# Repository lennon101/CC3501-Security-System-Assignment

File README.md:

# CC3501-Security-System-Assignment

##ABSTRACT
The purpose of this project was to investigate, design and implement an indoor security system that involved wireless communication, motion detection, image processing as well as additional features including a website with a video stream and control features. The projects objective has been to innovate an easy to use and affordable system ready for consumer use. This technical report provides and overview of the investigation, design and implementation done to deploy the project prototype.

##CC3501
- GROUP 5: Dane Lennon, Michael Grasso, Stuart Hinchliff, Stephanie Baker

##Project Features and Functionality
This system involves the integration of both hardware and software. It features a custom microprocessor PCB with a PIR motion detecting sensor communicating with a Raspberry Pi via XBee communications.
The features of this project include:
- Webserver application interface with full functionality
- The ability to arm and disarm the system
- Low power initial motion detection using a PIR sensor
- A second check for motion detection with complex image detection algorithms
- Voice configuration mode 
- Ability to email and save screenshots

##Hardware Design
###Printed Circuit Board Design
When designing this system, it was a priority that it must be as small and efficient as possible and only include the minimum number of necessary hardware features on the PCB, these included:
- PIR sensor for motion detection,
- LED to indicate motion detection 
- USB 2.0 port for power and necessary power supply regulations 
- Xbee for Zigbee communication
- JTAG header for SEGA programming 
- Battery holder for backup power

To reduce the size of this board further, a custom microprocessor board was designed to replace the standard shield for a Freescale Board. The Freescale FRDM-K20D50M schematic was used as a reference through the design process. Therefore, the microprocessor design, including the clock source and decoupling capacitor designs, was executed similarly to a professional board design. Figure 3 shows the completed PCB. 

###Central Hub and Peripherals
Implementing a security system with advanced features such as image processing and voice control was a task that could only be performed using a highly functional and heavily customizable device. The obvious choice was a Raspberry Pi, with capabilities of a small computer running the Linux operating system. The Raspberry Pi offers all of the features required by the group to design the central hub. Additionally, many open-source libraries are available for Linux to assist with the necessary features of the system such as the development of image processing, voice control and video streaming.

The Raspberry Pi B+ model features two USB ports and a 3.5mm audio jack, allowing the group to attach all required devices with ease. Additionally, a ribbon camera designed specifically for the Raspberry Pi is available, allowed for easy connection of a camera. The list of peripherals used in this project are:
Raspberry Pi Camera Board 
- USB 2.0 Microphone 
- Wi-Pi USB 2.0 Connector
- Powered USB 2.0 Hub

##Software Design
Robust was fundamental to the project. The system integrates scripts in C, C++, Python, HTML, JavaScript, and many external frameworks and libraries. The two main scripts were the C++ code running the main hub, and the Python code operating the webserver. Details of the functionality are described below.

###Server and Web-application
In order to appropriately develop the project, the target audience and their needs were carefully considered. It was assumed that average users would have no prior technical experience with embedded systems, so the software was designed to be user friendly.
A number of control methods were contemplated in the design process, including the use of a Bluetooth or web application. Upon review of similar products available it was determined that a web application provided the flexibility desired with: 
- Range of use (only an internet connection required 
- Security (authentication methods)
- Interface (intuitive GUI)
- Accessibility on a range of devices
- Potential for expansion
 
Various frameworks were considered to host the server. Due to its popularity and power, the lightweight, Python-based, framework called Flask was chosen. Further, a Bootstrap template was used for the webpage structure to improve the visual appeal and enhance user experience.

####Video Streaming
Surveillance is becoming increasingly prevalent in security systems and was the main drive for developing a web application. The implementation of this was inspired by Miguel Grinberg’s live video stream [1], which demonstrated how versatile Flask could be.
The main complication with using Python was its compatibility with the existing C++ code. It was found that a conflict occurred when attempting to access the camera from Python (for video streaming) and C++ (for image processing) scripts simultaneously. To overcome this, it was decided that saving an image from the C++ code and loading it to Python was the most feasible option. This came with a variety of advantages and disadvantages. It reduced the complexity of the code and it also provided a saved image for use in other processes, but the continuous read/write of images does consume system time. Sockets were also considered, but for image matrices proved complicated and prone to problem.

####Web-Application Control
The website comprises of three main pages: dashboard, view screenshots, and email configuration. The functionality of the website is as follows: (see Figure 2 for flowchart):
- Dashboard: View the live stream and execute available commands.
- Arm (Default): Receive data from the PCB. If a 1 (motion detected) is received image processing code is executed and an email is sent to the saved address.
- Disarm: Stop receiving data from the PCB.
- Save a SnapShot: Capture image of the live stream.
- Email a SnapShot: Send an email of the current image to the saved address.
- Enable Voice: Turn on voice control, allowing the user to configure via voice. o Disable Voice (Default): Turn off voice control.

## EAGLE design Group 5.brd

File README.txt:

To run the code, do it the way we do in labs: 
> $ cd SecuritySystem/build
> $ ./main

The main.cpp file - photo capture:
> There is one function that takes one photo as input and simply saves it
> This is the photo we will use for our stream
> It doesn't matter how often you upload the photo because there will always be an
  image with the right name there
> But the main loop is capturing an image every 10 loops
> The image is called "streamImage.jpg" and is found in the src directory

The main.cpp file - motion detection:
> There is one function that takes three frames and compares them for motion
> The difference between frame 1 and 3 is taken (3 being most recent capture)
> The difference between frame 2 and 3 is taken
> An "and" operation is performed on the differences so that only pixels that
  were changed in difference 1 AND difference 2 are counted (this eliminates
  a LOT of background noise)
> Then the image is converted to greyscale and thresholded 
> Thresholding could be upped from 25 to 30, but I found best accuracy with 25
  in my bedroom
> A very small amount of background noise may occur when a fan is on (I found that
  the clothes on my clothes line were moving just enough to trigger about 2-8 pixels
  of "difference") so the pixel count for "motion" has been set so that more than
  10 pixels of movement will signify motion. Might have to finetune this for the 
  robo club room.
> It picks up even small motion up to ~3m away, pls appreciate how stupid I felt jumping
  up and down on my bed and yelling "TAKE PHOTO" at my Pi to test this.
> It should pick up motion further away, still need to run those tests.
> If motion is detected, the images are saved. And this is where we need to add the email
  functionality.

The main.cpp file - voice recognition
> There are 5 commands as it stands, but I'm happy to add more.
> "HELLO" - puts the voice control system into configuration mode, the system WILL NOT LISTEN
  for any other commands until you say "HELLO" to wake it up.
> "ARM" - arms the system, we still need to talk about what we're going to classify as "arming
  the system".
> "DISARM" - disarms the system
> "TAKE PHOTO" - tests the motion detection. Ask the program to take a photo and it will capture
  three frames, and it will verbally tell you whether it detected motion or not. GREAT way to
  check that motion detection is working as it should, and it will let us know if we need to
  fine tune for background noise in a bigger room. Probably my favourite voice control feature.
> "GOODBYE" - puts the voice control back into "not listening" mode. He won't listen for anything
  except the word "HELLO", so the loop will run full speed and the stream will be updated constantly.
> If we want to change these PLEASE PLEASE PLEASE let me do it, I've spent a lot of time
  working on the algorithms behind language models and dictation and I have a pretty deep
  understanding of what's going to work best -- and on that note I've tested a lot of words for the
  above functions and these are the ones I've had the most success and highest accuracy rate with.
> If any of you find that voice control isn't understanding you when you say one of the 
  commands, send me a voice clip of you saying the command and I'll add your pronunciation of the
  command to our dictation model.

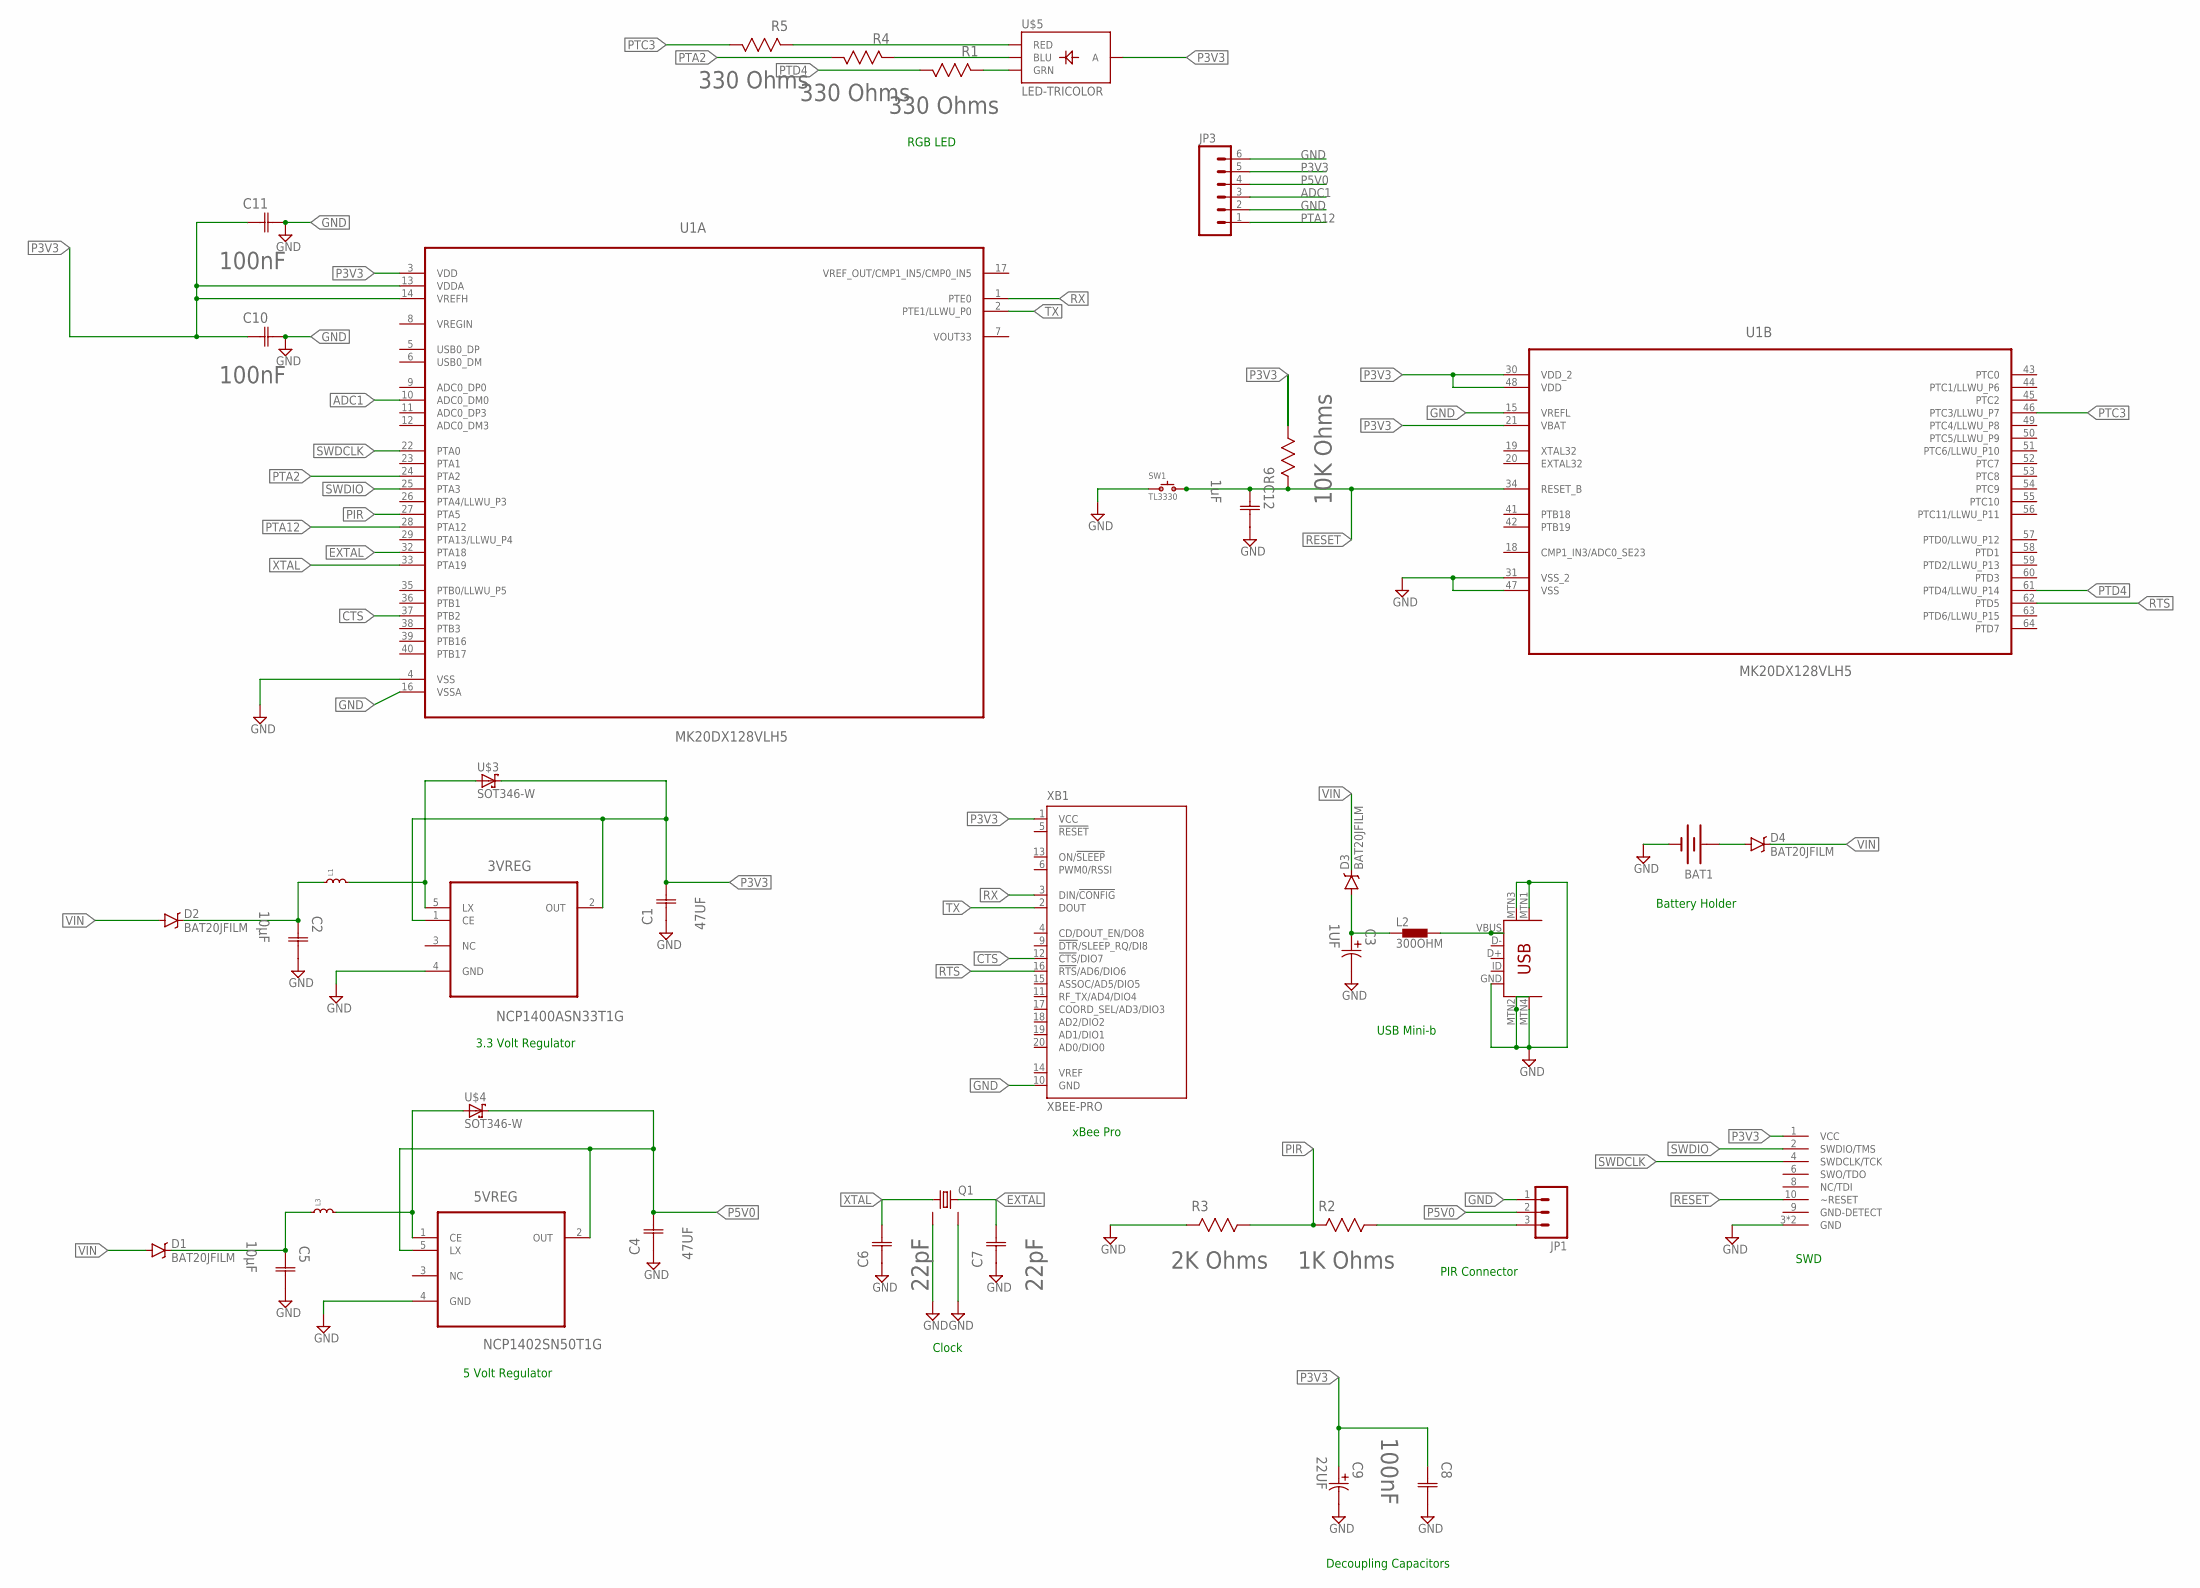
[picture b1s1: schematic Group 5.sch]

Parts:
3VREG: NCP1400ASN33T1G; SOT95P275X110-5N
5VREG: NCP1402SN50T1G; SOT95P275X110-5N
BAT1: BATTERY20PTH; BATTCOM_20MM_PTH
C1, C4: 47UF; CAPCP6032X280N
C2, C5: 10µF; CAPCP6032X280N
C3: 1UF; CAPAE430X610N
C6, C7: 22pF; CAPC1608X85N
C8, C10, C11: 100nF; CAPC2013X95N
C9: 22UF; CAPAE430X610N
C12: 1uF; CAPC1608X94N
D1, D2, D3, D4: BAT20JFILM; SOD-323
JP1: M03PTH; 1X03
JP3: M06LONGPADS; 1X06_LONGPADS
L1, L3: INDUCTOR-SDR0403; SDR0403
L2: 300OHM; 0402
Q1: CRYSTALCTS406; CTS406
R1, R4, R5: 330 Ohms; RESC2013X65N
R2: 1K Ohms; RESC3216X71N
R3: 2K Ohms; RESC3216X71N
R6: 10K Ohms; RESC1608X60N
SW1: TL3330
U1: MK20DX128VLH5; QFP50P1200X1200X160-64N
U$1: 2X5_0.05"_CORTEX_DEBUGTH_NOKEY_UNSHROUDED; 2X5_0.05"_TH_NS
U$2: USB-MINIB-5PIN; USB-MINIB
U$3, U$4: SOT346-W
U$5: LED-TRICOLOR; LED-TRICOLOR-SMD
XB1: XBEE-PRO

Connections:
ADC1: JP3.3, U1.10 (ADC0_DM0)
CTS: U1.37 (PTB2), XB1.12 (!CTS!/DIO7)
EXTAL: C7.2 (C2), Q1.3 (2), U1.32 (PTA18)
GND: 3VREG.4 (GND), 5VREG.4 (GND), BAT1.2 (-), C1.1 (C1), C2.2 (C2), C3.2, C4.1 (C1), C5.2 (C2), C6.1 (C1), C7.1 (C1), C8.2 (C2), C9.2, C10.2 (C2), C11.2 (C2), C12.2 (C2), JP1.1, JP3.2, JP3.6, Q1.2 (GND1), Q1.4 (GND2), R3.2 (R2), SW1.1, U1.4 (VSS), U1.15 (VREFL), U1.16 (VSSA), U1.31 (VSS_2), U1.47 (VSS), U$1.3 (GND), U$1.5 (GND), U$2.GND, U$2.MTN1 (MTN2), U$2.MTN2 (MTN3), U$2.MTN3 (MTN1), U$2.MTN4, XB1.10 (GND)
unnamed: 3VREG.5 (LX), L1.2, U$3.1 (A)
unnamed: L2.2, U$2.VBUS
unnamed: 5VREG.1 (CE), L3.2, U$4.1 (A)
unnamed: JP1.3, R2.1 (R1)
unnamed: R1.2 (R2), U$5.G (GRN)
unnamed: R4.2 (R2), U$5.B (BLU)
unnamed: R5.2 (R2), U$5.R (RED)
unnamed: BAT1.1 (+), D4.A
P3V3: 3VREG.1 (CE), 3VREG.2 (OUT), C1.2 (C2), C8.1 (C1), C9.1, C10.1 (C1), C11.1 (C1), JP3.5, R6.1 (R1), U1.3 (VDD), U1.13 (VDDA), U1.14 (VREFH), U1.21 (VBAT), U1.30 (VDD_2), U1.48 (VDD), U$1.1 (VCC), U$3.3 (C), U$5.A, XB1.1 (VCC)
P5V0: 5VREG.2 (OUT), 5VREG.5 (LX), C4.2 (C2), JP1.2, JP3.4, U$4.3 (C)
PIR: R2.2 (R2), R3.1 (R1), U1.27 (PTA5)
PTA2: R4.1 (R1), U1.24 (PTA2)
PTA12: JP3.1, U1.28 (PTA12)
PTC3: R5.1 (R1), U1.46 (PTC3/LLWU_P7)
PTD4: R1.1 (R1), U1.61 (PTD4/LLWU_P14)
RE: C2.1 (C1), D2.C, L1.1
RE3: C5.1 (C1), D1.C, L3.1
RESET: C12.1 (C1), R6.2 (R2), SW1.2, U1.34 (RESET_B), U$1.10 (~RESET)
RTS: U1.62 (PTD5), XB1.16 (!RTS!/AD6/DIO6)
RX: U1.1 (PTE0), XB1.3 (DIN/!CONFIG)
SWDCLK: U1.22 (PTA0), U$1.4 (SWDCLK/TCK)
SWDIO: U1.25 (PTA3), U$1.2 (SWDIO/TMS)
TX: U1.2 (PTE1/LLWU_P0), XB1.2 (DOUT)
VIN: D1.A, D2.A, D3.C, D4.C
VIN3: C3.1, D3.A, L2.1
XTAL: C6.2 (C2), Q1.1, U1.33 (PTA19)

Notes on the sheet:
Clock
5 Volt Regulator
3.3 Volt Regulator
USB Mini-b
PIR Connector
xBee Pro
SWD
Battery Holder
Decoupling Capacitors
RGB LED

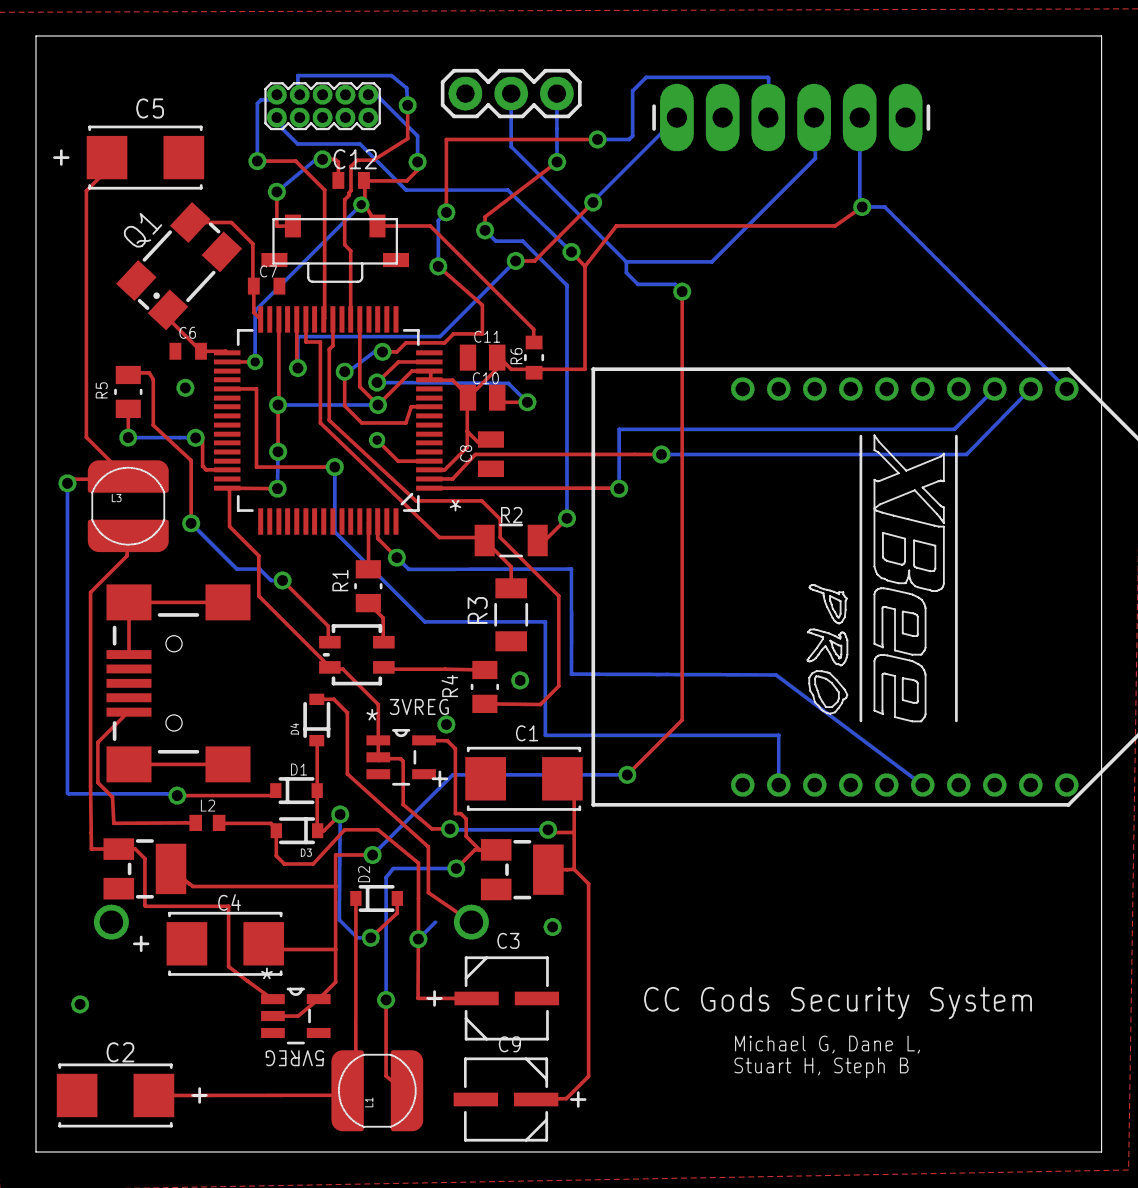
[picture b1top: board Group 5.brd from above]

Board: 2 copper layers, 59.2 x 62.0 mm, 39 parts (1 on the bottom side), 30 nets.

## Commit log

2016-07-05 cloned private repo to public repo for viewing purposes
2016-07-05 update read

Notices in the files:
parts and their libraries:
SparkFun-Electromechanical: Licensing: Creative Commons ShareAlike 4.0 International - https://creativecommons.org/licenses/by-sa/4.0
